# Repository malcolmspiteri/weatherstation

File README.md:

# weatherstation
A DIY weather station just for fun

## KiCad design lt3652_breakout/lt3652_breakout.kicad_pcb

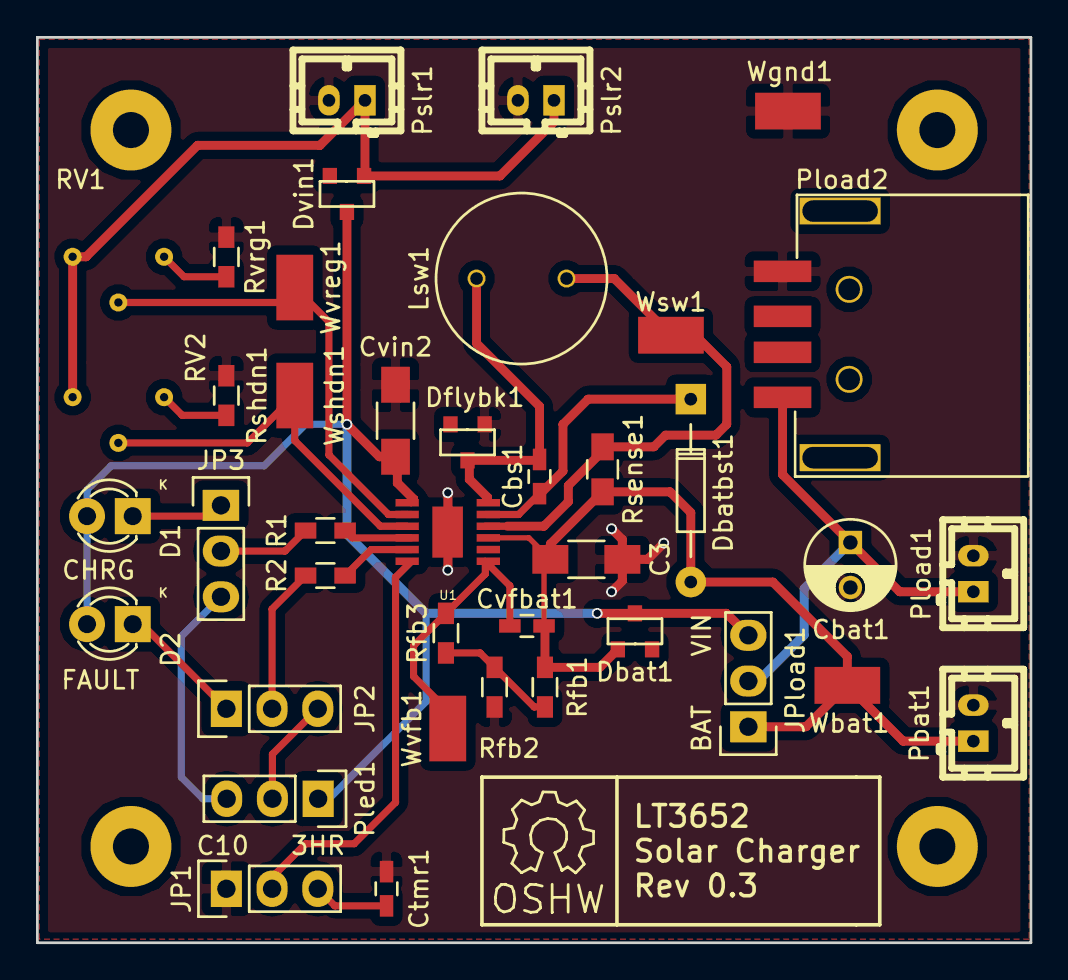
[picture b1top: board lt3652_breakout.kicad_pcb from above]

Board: 2 copper layers, 55.2 x 50.3 mm, 40 parts (0 on the bottom side), 24 nets.

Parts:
C3: 10uF; C_1206_HandSoldering
Cbat1: 100uF; C_Radial_D5_L6_P2.5
Cbs1: 1uF; C_0603_HandSoldering
Ctmr1: 0.68µF; C_0603_HandSoldering
Cvfbat1: 22pF; C_0603_HandSoldering
Cvin2: 10uF; C_1206_HandSoldering
D1: 3mm GRN; LED-3MM
D2: 3mm RED; LED-3MM
Dbat1: D_Schottky_Small_ZLLS500; DIODES_INC_ZLLS500
Dbatbst1: D_Small; Diode_DO-35_SOD27_Horizontal_RM10
Dflybk1: ZLLS500; DIODES_INC_ZLLS500
Dvin1: D_Schottky_Small_ZLLS500; DIODES_INC_ZLLS500
JP1: TIMER OPT; Pin_Header_Straight_1x03
JP2, JP3: JUMPER3; Pin_Header_Straight_1x03
JPload1: JUMPER3; Pin_Header_Straight_1x03
Lsw1: 10uH; PANASONIC_ELC09D100F
Pbat1: JST PH; b2b-ph-kl
Pled1: CONN_01X03; Pin_Header_Straight_1x03
Pload1: JST PH; b2b-ph-kl
Pload2: USB_A; WURTH_ELEKTRONIK_629104151021
Pslr1, Pslr2: JST PH; b2b-ph-kl
R1, R2: 10K; R_0603_HandSoldering
RV1, RV2: POT; Bourns_3362P_Trimmer
Rfb1: 90k; R_0603_HandSoldering
Rfb2: 330k; R_0603_HandSoldering
Rfb3: 179k; R_0603_HandSoldering
Rsense1: 250mO; C_0805_HandSoldering
Rshdn1: 10K; R_0603_HandSoldering
Rvrg1: 10K; R_0603_HandSoldering
U1: LT3652; LT3652MSE_HandSoldering
Wbat1: TEST_1P; HARWIN_S1751-46
Wgnd1: TEST_1P; HARWIN_S1751-46
Wshdn1: TEST_1P; HARWIN_S1751-46
Wsw1: TEST_1P; HARWIN_S1751-46
Wvfb1: TEST_1P; HARWIN_S1751-46
Wvreg1: TEST_1P; HARWIN_S1751-46

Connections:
/BAT: C3.1, Cvfbat1.1, Dbat1.3, Dbatbst1.2, JPload1.1, Pbat1.1, Rfb1.1, Rsense1.2, U1.9, Wbat1.1
/BOOST: Cbs1.1, Dbatbst1.1, U1.11
/SENSE: Lsw1.2, Rsense1.1, U1.10, Wsw1.1
/SHDN: RV2.2, U1.3, Wshdn1.1
/SW: Cbs1.2, Dflybk1.1, Lsw1.1, U1.12
/VFB: Cvfbat1.2, Rfb3.2, U1.7, Wvfb1.1
/VIN: Cvin2.2, D1.2, D2.2, Dbat1.1, Dvin1.1, JPload1.3, Pled1.1, U1.1
/VIN_REG: RV1.2, U1.2, Wvreg1.1
GND: C3.2, Cbat1.2, Ctmr1.2, Cvin2.1, Dflybk1.3, JP1.1, Pbat1.2, Pload1.2, Pload2.4, Pslr1.2, Pslr2.2, Rfb2.2, Rshdn1.2, Rvrg1.2, U1.13, Wgnd1.1
unnamed: Cbat1.1, JPload1.2, Pload1.1, Pload2.1
unnamed: Ctmr1.1, JP1.3
unnamed: D1.1, JP3.1
unnamed: D2.1, JP2.1
unnamed: Dvin1.3, Pslr1.1, Pslr2.1, RV1.1, RV2.1
unnamed: JP1.2, U1.6
unnamed: JP2.2, R2.2
unnamed: JP2.3, Pled1.2
unnamed: JP3.2, R1.2
unnamed: JP3.3, Pled1.3
unnamed: R1.1, U1.4
unnamed: R2.1, U1.5
unnamed: RV1.3, Rvrg1.1
unnamed: RV2.3, Rshdn1.1
unnamed: Rfb1.2, Rfb2.1, Rfb3.1

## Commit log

2016-02-13 Initial upload of collector unit hardware design
2016-02-14 Working on the power unit
2016-02-15 Initial upload of LT3652 breakout sub-project
2016-02-15 Further work on the power unit
2016-02-16 WIP on LT3652 breakout
2016-02-16 LT3652 Breakout Rev 0.1
2016-02-17 Started work on Rev 0.2, with the aim of using trimmer to configure the LT3652
2016-02-18 Fixed minimum length of LT3652 footprint
2016-02-22 WIP on Rev 0.2
2016-02-23 WIP of Rev 0.2
2016-03-02 Relaid pcb to the size of the box that will house it
2016-03-02 Added option to connect load directly to Vin. Also routed the PCB
2016-03-02 Release of Rev 0.2 of the LT3652 breakout
2016-03-07 Upload of Rev 0.3
2016-03-29 Initial commit of air quality unit
2016-12-16 Added some reference docs and gerber output
